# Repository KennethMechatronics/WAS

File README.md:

# WAS — WiFi Activated Switcher

**An ESP32-C3-based interface for controlling an existing three-speed ventilation system through Wi-Fi, MQTT and Home Assistant.**

## Overview

WAS adds network control to a conventional ventilation control panel without replacing its existing controls. It uses two outputs to emulate operation of the panel's switching interface, reads the actual ventilation setting through feedback inputs, and reports that setting to an MQTT broker.

Commands can be issued from Home Assistant or any MQTT client. Changes made using the original physical panel are also detected and published, keeping the reported state in sync with the equipment.

The project combines a custom PCB, an ESP32-C3, an RGB status indicator, a 3D-modelled enclosure and C++ firmware developed with PlatformIO.

## Features

- **Three ventilation settings:** `Min`, `Normal` and `Max`.
- **MQTT control:** receive speed requests and publish the detected current setting.
- **Physical-panel feedback:** sense the `Normal` and `Max` states; neither active is interpreted as `Min`.
- **Closed-loop switching:** operate the switching outputs, read back the actual setting and retry if needed.
- **Manual control preserved:** detect a change made at the existing panel and report it over MQTT.
- **RGB status indication:** display connection, switching and state/error information using an LP5817 LED driver.
- **Custom hardware:** KiCad PCB, component libraries, Autodesk Inventor assembly and enclosure models.

## Project images

### PCB

### PCB 3D views

| Front | Back |
| :---: | :---: |
|  |  |

### Schematic overview

Additional PCB layer views and review renders are available in [`Electronics/WAS/Review images/`](Electronics/WAS/Review%20images/).

## How it works

1. The ESP32-C3 connects to the configured Wi-Fi network and MQTT broker.
2. It subscribes to `WAS/setVentilationState` for speed requests.
3. On a request, it compares the requested setting with the setting detected from its feedback inputs.
4. If they differ, it pulses the panel-bypass outputs and checks the feedback again, retrying within a defined limit.
5. It publishes the detected setting on `WAS/currentVentilationState`. It also reports changes initiated at the physical panel and periodically republishes the state.

> **Safety:** This is a custom retrofit electronics project, not a certified universal ventilation controller. Check electrical compatibility, isolation, power supply requirements and applicable electrical safety requirements before connecting it to equipment. The firmware's MQTT connection uses the configured broker on port `1883`; do not expose an unsecured broker directly to the internet.

## License
Firmware: MIT

Hardware: CERN-OHL-P-2.0

---

**Created by [Kenneth Paulsen](https://github.com/KennethMechatronics)** — a personal project combining mechanical design, PCB development and embedded programming.

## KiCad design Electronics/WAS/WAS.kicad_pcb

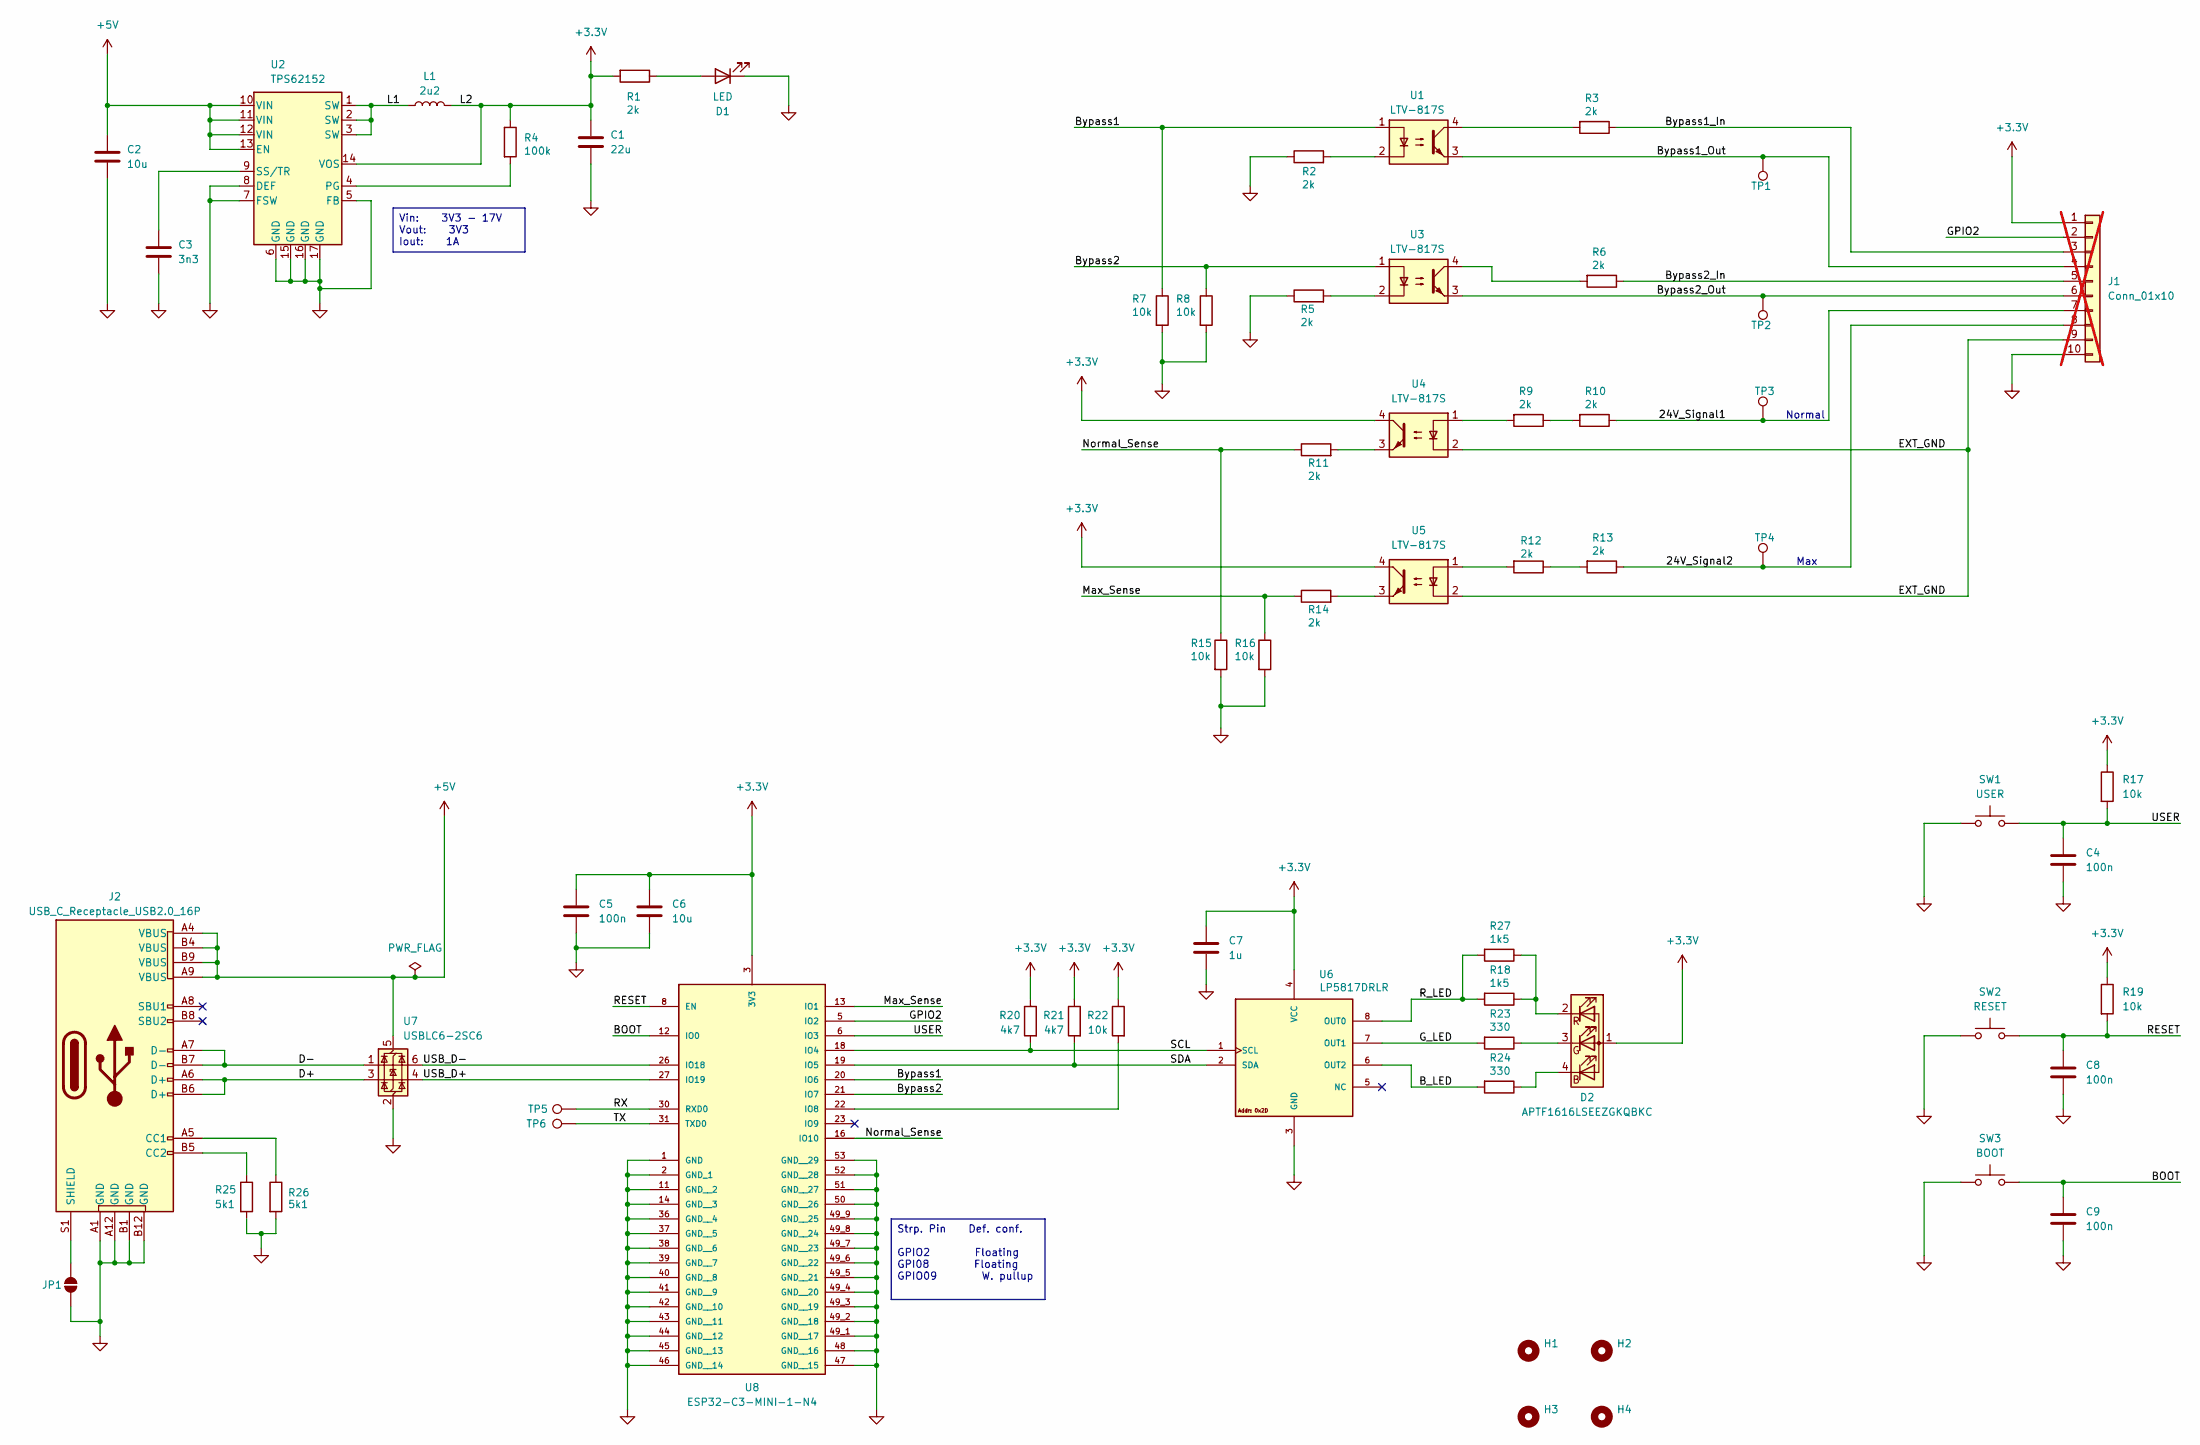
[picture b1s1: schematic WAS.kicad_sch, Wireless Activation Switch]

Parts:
C1: 22u; C_0805_2012Metric; LCSC C45783
C2: 10u; C_1206_3216Metric; LCSC C13585
C3: 3n3; C_0603_1608Metric; LCSC C1613
C4, C5, C8, C9: 100n; C_0402_1005Metric; LCSC C1525
C6: 10u; C_0603_1608Metric; LCSC C19702
C7: 1u; C_0603_1608Metric; LCSC C15849
D1: LED; LED_0805_2012Metric; LCSC C2297
D2: APTF1616LSEEZGKQBKC; SON4_APTF1616LSEEZGKQBKC_KNB; LCSC C3019103
H1, H2, H3, H4: MountingHole_2.2mm_M2_ISO14580
J1: Conn_01x10; PinHeader_1x10_P2.54mm_Vertical; not fitted
J2: USB_C_Receptacle_USB2.0_16P; USB_C_Receptacle_HRO_TYPE-C-31-M-12; LCSC C165948
JP1: SolderJumper_2_Open; SolderJumper-2_P1.3mm_Open_TrianglePad1.0x1.5mm
L1: 2u2; YHNR4020-2R2M; LCSC C2926400
R1, R3, R6, R9, R10, R12, R13: 2k; R_1206_3216Metric; LCSC C17944
R2, R5, R11, R14: 2k; R_0402_1005Metric; LCSC C4109
R4: 100k; R_0402_1005Metric; LCSC C25741
R7, R8, R15, R16, R17, R19, R22: 10k; R_0402_1005Metric; LCSC C25744
R18, R27: 1k5; R_0402_1005Metric; LCSC C25867
R20, R21: 4k7; R_0402_1005Metric; LCSC C25900
R23, R24: 330; R_0402_1005Metric; LCSC C25104
R25, R26: 5k1; R_0402_1005Metric; LCSC C25905
SW1: USER; SW_TS-1088-AR02016; LCSC C720477
SW2: RESET; SW_TS-1088-AR02016; LCSC C720477
SW3: BOOT; SW_TS-1088-AR02016; LCSC C720477
TP1, TP2, TP3, TP4, TP5, TP6: TestPoint; TestPoint_D0.5
U1, U3, U4, U5: LTV-817S; SMDIP-4_W9.53mm; LCSC C109227
U2: TPS62152; VQFN-16-1EP_3x3mm_P0.5mm_EP1.68x1.68mm_ThermalVias; LCSC C2070611
U6: LP5817DRLR; SOT-583-8; PARTREV MARCH 2025; LCSC C47262829
U7: USBLC6-2SC6; SOT-23-6; LCSC C7519
U8: ESP32-C3-MINI-1-N4; XCVR_ESP32-C3-MINI-1-N4; PARTREV v1.0; LCSC C2838502

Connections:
+3.3V: C1.1, C5.1, C6.1, C7.1, D2.1 (A), J1.1, L1.2, R1.2, R4.1, R17.1, R19.1, R20.1, R21.1, R22.1, U2.14 (VOS), U4.4, U5.4, U6.4 (VCC), U8.3 (3V3)
+5V: C2.1, J2.A4 (VBUS), J2.A9 (VBUS), J2.B4 (VBUS), J2.B9 (VBUS), U2.10 (VIN), U2.11 (VIN), U2.12 (VIN), U2.13 (EN), U7.5 (VBUS)
/24V_Signal1: J1.7, R10.1, TP3.1
/24V_Signal2: J1.8, R13.1, TP4.1
/BOOT: C9.1, SW3.2, U8.12 (IO0)
/B_LED: R24.2, U6.6 (OUT2)
/Bypass1: R7.1, U1.1, U8.20 (IO6)
/Bypass1_In: J1.3, R3.1
/Bypass1_Out: J1.4, TP1.1, U1.3
/Bypass2: R8.1, U3.1, U8.21 (IO7)
/Bypass2_In: J1.5, R6.1
/Bypass2_Out: J1.6, TP2.1, U3.3
/D+: J2.A6 (D+), J2.B6 (D+), U7.3 (I/O2)
/D-: J2.A7 (D-), J2.B7 (D-), U7.1 (I/O1)
/EXT_GND: J1.9, U4.2, U5.2
/GPIO2: J1.2, U8.5 (IO2)
/G_LED: R23.2, U6.7 (OUT1)
/L1: L1.1, U2.1 (SW), U2.2 (SW), U2.3 (SW)
/Max_Sense: R14.1, R16.1, U8.13 (IO1)
/Normal_Sense: R11.1, R15.1, U8.16 (IO10)
/RESET: C8.1, R19.2, SW2.2, U8.8 (EN)
/RX: TP5.1, U8.30 (RXD0)
/R_LED: R18.2, R27.2, U6.8 (OUT0)
/SCL: R20.2, U6.1 (SCL), U8.18 (IO4)
/SDA: R21.2, U6.2 (SDA), U8.19 (IO5)
/TX: TP6.1, U8.31 (TXD0)
/USB_D+: U7.4 (I/O2), U8.27 (IO19)
/USB_D-: U7.6 (I/O1), U8.26 (IO18)
/USER: C4.1, R17.2, SW1.2, U8.6 (IO3)
GND: C1.2, C2.2, C3.2, C4.2, C5.2, C6.2, C7.2, C8.2, C9.2, D1.1 (K), J1.10, J2.A1 (GND), J2.A12 (GND), J2.B1 (GND), J2.B12 (GND), JP1.2 (B), R2.1, R5.1, R7.2, R8.2, R15.2, R16.2, R25.2, R26.2, SW1.1, SW2.1, SW3.1, U2.5 (FB), U2.6 (GND), U2.7 (FSW), U2.8 (DEF), U2.15 (GND), U2.16 (GND), U2.17 (GND), U6.3 (GND), U7.2 (GND), U8.1 (GND), U8.2 (GND_1), U8.11 (GND__2), U8.14 (GND__3), U8.36 (GND__4), U8.37 (GND__5), U8.38 (GND__6), U8.39 (GND__7), U8.40 (GND__8), U8.41 (GND__9), U8.42 (GND__10), U8.43 (GND__11), U8.44 (GND__12), U8.45 (GND__13), U8.46 (GND__14), U8.47 (GND__15), U8.48 (GND__16), U8.49_1 (GND__17), U8.49_2 (GND__18), U8.49_3 (GND__19), U8.49_4 (GND__20), U8.49_5 (GND__21), U8.49_6 (GND__22), U8.49_7 (GND__23), U8.49_8 (GND__24), U8.49_9 (GND__25), U8.50 (GND__26), U8.51 (GND__27), U8.52 (GND__28), U8.53 (GND__29)
unnamed: D1.2 (A), R1.1
unnamed: D2.4 (BK), R24.1
unnamed: D2.3 (GK), R23.1
unnamed: D2.2 (RK), R18.1, R27.1
unnamed: J2.A5 (CC1), R26.1
unnamed: J2.B5 (CC2), R25.1
unnamed: J2.S1 (SHIELD), JP1.1 (A)
unnamed: R2.2, U1.2
unnamed: R3.2, U1.4
unnamed: R5.2, U3.2
unnamed: R6.2, U3.4
unnamed: R9.2, U4.1
unnamed: R9.1, R10.2
unnamed: R11.2, U4.3
unnamed: R12.1, R13.2
unnamed: R12.2, U5.1
unnamed: R14.2, U5.3
unnamed: R4.2, U2.4 (PG)
unnamed: C3.1, U2.9 (SS/TR)
unnamed: R22.2, U8.22 (IO8)

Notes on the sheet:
Normal
Max
Vin: 3V3 - 17V Vout: 3V3 Iout: 1A
Strp. Pin Def. conf. GPIO2 Floating GPI08 Floating GPIO09 W. pullup

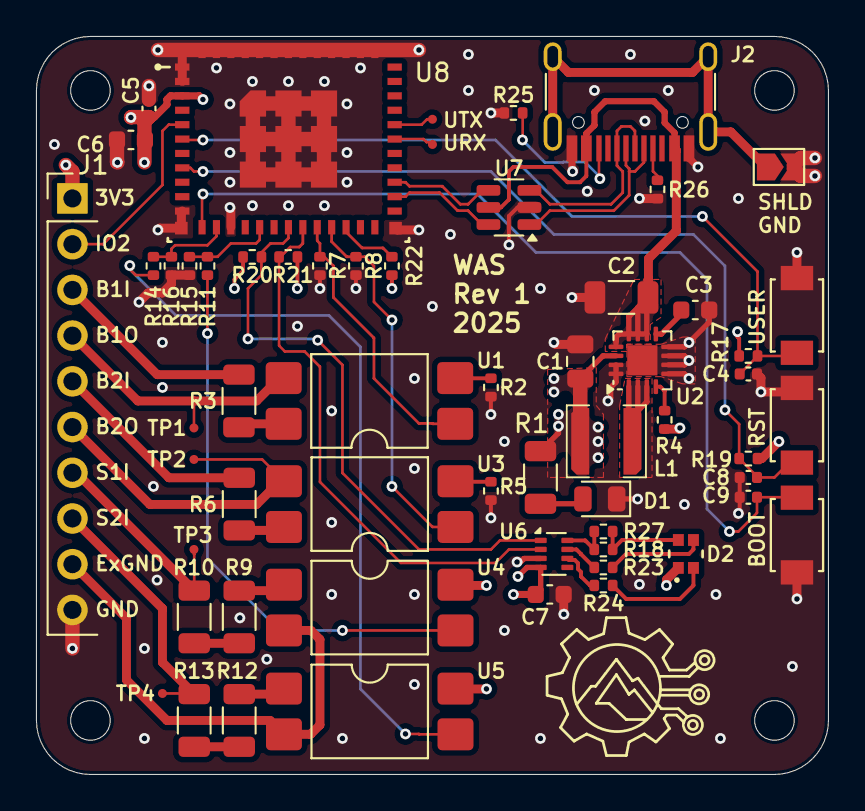
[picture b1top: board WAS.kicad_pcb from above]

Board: 4 copper layers, 44.0 x 41.0 mm, 63 parts (0 on the bottom side), 50 nets.

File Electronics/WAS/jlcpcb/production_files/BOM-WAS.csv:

Comment,Designator,Footprint,LCSC,Quantity
100k,R4,R_0402_1005Metric,C25741,1
100n,"C4,C5,C8,C9",C_0402_1005Metric,C1525,4
10k,"R15,R16,R17,R19,R22,R7,R8",R_0402_1005Metric,C25744,7
10u,C2,C_1206_3216Metric,C13585,1
10u,C6,C_0603_1608Metric,C19702,1
1k5,"R18,R27",R_0402_1005Metric,C25867,2
1u,C7,C_0603_1608Metric,C15849,1
22u,C1,C_0805_2012Metric,C45783,1
2k,"R1,R10,R12,R13,R3,R6,R9",R_1206_3216Metric,C17944,7
2k,"R11,R14,R2,R5",R_0402_1005Metric,C4109,4
2u2,L1,YHNR4020-2R2M,C2926400,1
330,"R23,R24",R_0402_1005Metric,C25104,2
3n3,C3,C_0603_1608Metric,C1613,1
4k7,"R20,R21",R_0402_1005Metric,C25900,2
5k1,"R25,R26",R_0402_1005Metric,C25905,2
APTF1616LSEEZGKQBKC,D2,SON4_APTF1616LSEEZGKQBKC_KNB,C3019103,1
BOOT,SW3,SW_TS-1088-AR02016,C720477,1
ESP32-C3-MINI-1-N4,U8,XCVR_ESP32-C3-MINI-1-N4,C2838502,1
LED,D1,LED_0805_2012Metric,C2297,1
LP5817DRLR,U6,SOT-583-8,C47262829,1
LTV-817S,"U1,U3,U4,U5",SMDIP-4_W9.53mm,C109227,4
RESET,SW2,SW_TS-1088-AR02016,C720477,1
TPS62152,U2,VQFN-16-1EP_3x3mm_P0.5mm_EP1.68x1.68mm_ThermalVias,C2070611,1
USBLC6-2SC6,U7,SOT-23-6,C7519,1
USB_C_Receptacle_USB2.0_16P,J2,USB_C_Receptacle_HRO_TYPE-C-31-M-12,C165948,1
USER,SW1,SW_TS-1088-AR02016,C720477,1
